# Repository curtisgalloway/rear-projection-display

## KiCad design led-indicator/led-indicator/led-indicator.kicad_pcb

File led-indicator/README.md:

# RGBW Indicator Board — LED Indicator

KiCad 8 schematic for a 12-LED addressable RGBW indicator panel. Replaces incandescent bulbs in a rear-projection indicator display. Target: ~2×3 inch, 2-layer, JLCPCB fabrication + assembly.

## Bill of Materials

| Ref | Qty | Value / Description | Package | JLCPCB Part | Notes |
|-----|-----|---------------------|---------|-------------|-------|
| D1–D12 | 12 | SK6812 RGBW addressable LED | 5050 SMD (5.0×5.0mm) | C2890364 (SK6812-EC15) | Assign footprint `LED_SMD:LED_SK6812_PLCC4_5.0x5.0mm_P3.2mm` |
| C1–C12 | 12 | 100nF ceramic capacitor | 0603 SMD | C14663 | Per-LED decoupling, place close to each LED |
| C13 | 1 | 1000µF 10V electrolytic | Radial 8mm dia, 3.5mm pitch | C6185 (100µF) or C6971 (1000µF SMD) | Bulk input decoupling; check JLCPCB Basic parts at order time |
| R1 | 1 | 330Ω resistor | 0603 SMD | C23138 | Data line series resistor (DIN protection) |
| U1 | 1 | 74AHCT125 quad 3-state buffer | SOIC-14 | C7084 | 3.3V→5V level shifter; Basic part |
| J1 | 1 | DC barrel jack 2.1mm×5.5mm, center-positive | Through-hole | — | PJ-102AH or equivalent; assign footprint manually |
| J2 | 1 | JST-XH 3-pin header (5V, GND, DATA) | Through-hole, 2.5mm pitch | C2681542 | Pin 1=5V (via SJ1), Pin 2=GND, Pin 3=DATA |
| SJ1 | 1 | Solder jumper, 2-pin, normally OPEN | — | — | Isolates J2 5V pin from main rail; close to back-power from controller |

## Schematic Notes

**Daisy-chain direction:** DATA_IN → R1 → D1.DIN → D1.DOUT → D2.DIN → … → D12.DOUT (leave D12.DOUT unconnected or add test point)

**330Ω resistor (R1):** Limits current transients and protects against transmission-line reflections on the data line. Place between U1 output and D1.DIN.

**Solder jumper SJ1:** Normally open. Connects the 5V pin on J2 to the main +5V rail. Close only when powering the board from the controller side (low-power testing). Leave open when using the barrel jack (J1) to avoid fighting two supplies.

**74AHCT125 (U1):**
- Channel 1 (pins 1/2/3): active — ~OE tied to GND (pin 1), A=DATA_IN (pin 2), Y=data out to R1 (pin 3)
- Channels 2–4: disabled — ~OE pins (4, 10, 13) tied to +5V; A inputs (5, 9, 12) tied to GND; Y outputs (6, 8, 11) no-connect

## Footprints to Assign Before PCB Layout

| Ref | Footprint |
|-----|-----------|
| D1–D12 | `LED_SMD:LED_SK6812_PLCC4_5.0x5.0mm_P3.2mm` *(already set)* |
| J1 | `Connector_BarrelJack:BarrelJack_Horizontal_PJ-102AH` or similar 2.1mm barrel |
| SJ1 | `Jumper:SolderJumper-2_P1.3mm_Open_Pad1.0x1.5mm` |
| C13 | Verify package matches the part ordered (radial THT or SMD) |

## Power Budget (rough)

SK6812 at full white: ~60mA per LED × 12 = 720mA + 5V logic overhead. Use a ≥1A 5V supply on J1. The 1000µF bulk cap (C13) handles the high-frequency current draw of the WS2812-protocol burst updates.

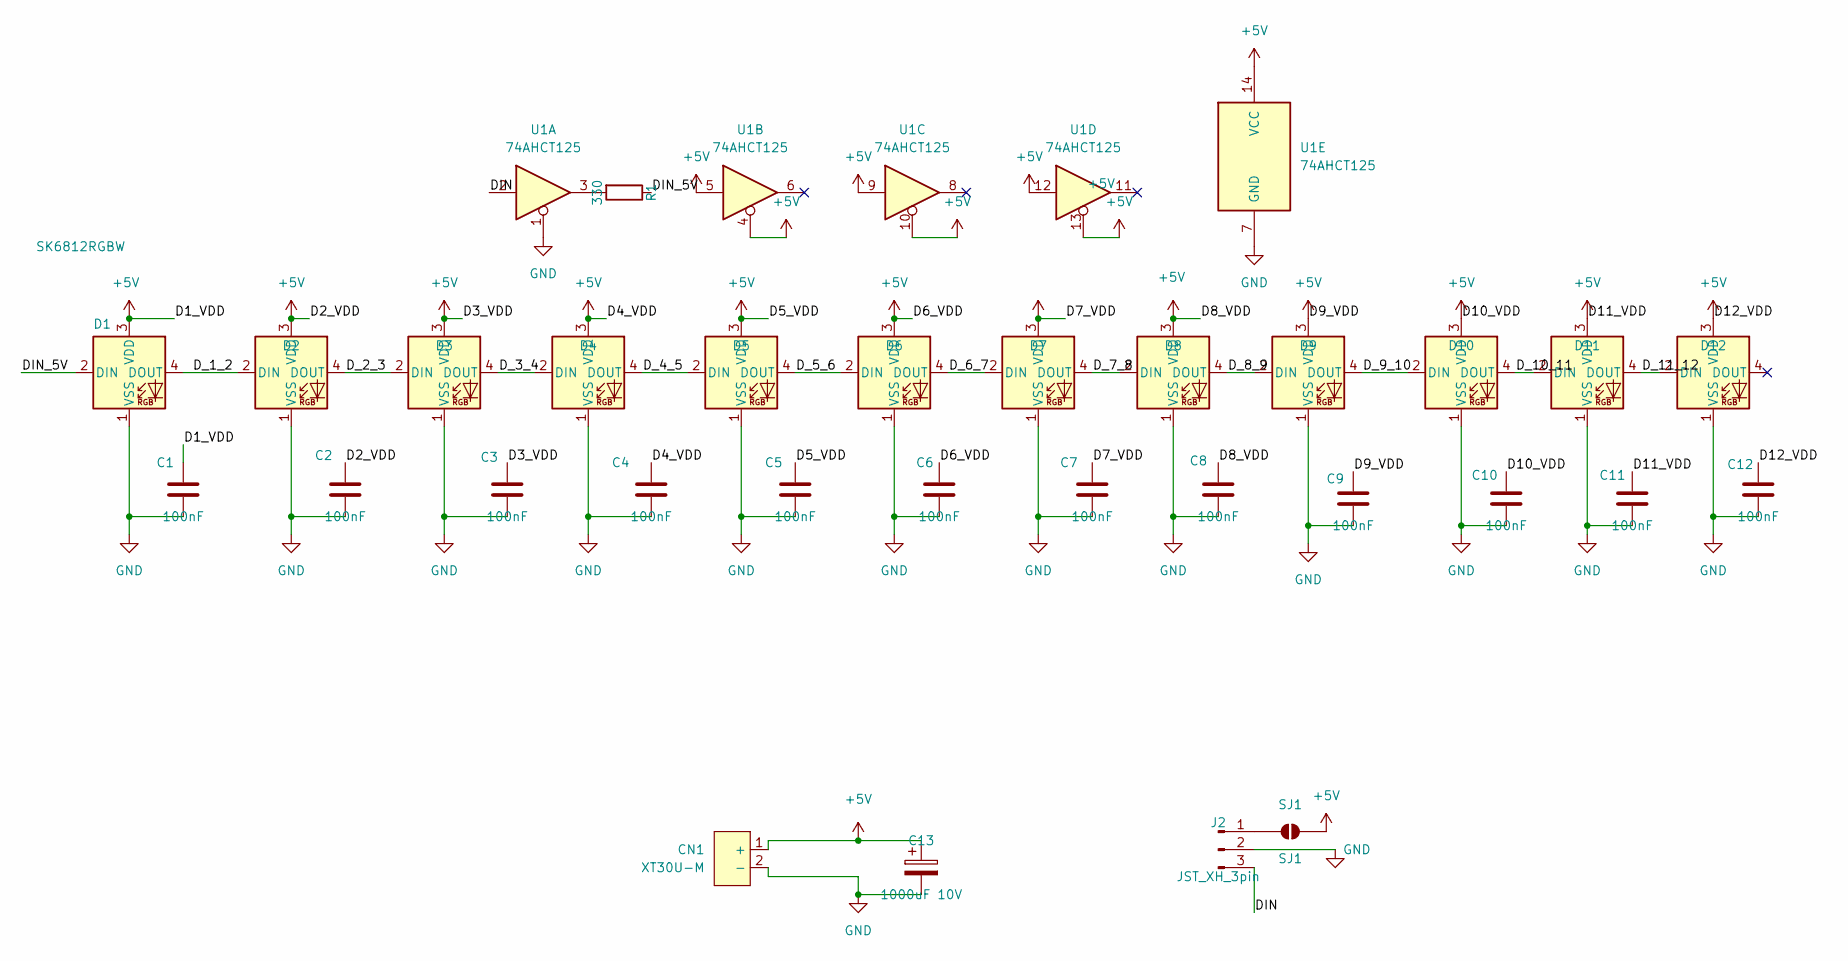
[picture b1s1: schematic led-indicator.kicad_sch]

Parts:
C1, C2, C3, C4, C5, C6, C7, C8, C9, C10, C11, C12: 100nF; C_0603_1608Metric; MPN CC0603KRX7R9BB104; LCSC C14663
C13: 1000uF 10V; CP_Radial_D8.0mm_P3.50mm; MPN GR108M010F12RR0VL4FP0; LCSC C3299
CN1: XT30U-M; AMASS_XT30U-M_1x02_P5.0mm_Vertical; MPN XT30U-M; LCSC Part C99101
D1, D2, D3, D4, D5, D6, D7, D8, D9, D10, D11, D12: SK6812RGBW; LED_SK6812_PLCC4_5.0x5.0mm_P3.2mm; MPN XL-5050RGBWC-WS2812B; LCSC C22464516
J2: JST_XH_3pin; JST_XH_B3B-XH-A_1x03_P2.50mm_Vertical; MPN B3B-XH-A(LF)(SN); LCSC C144394
R1: 330; R_0603_1608Metric; MPN 0603WAF3300T5E; LCSC C23138
SJ1: SJ1; SolderJumper-2_P1.3mm_Open_RoundedPad1.0x1.5mm
U1: 74AHCT125; SOIC-14_3.9x8.7mm_P1.27mm; MPN 74AHCT125S14-13; LCSC C842299

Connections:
+5V: C1.1, C2.1, C3.1, C4.1, C5.1, C6.1, C7.1, C8.1, C9.1, C10.1, C11.1, C12.1, C13.1, CN1.1 (+), D1.3 (VDD), D2.3 (VDD), D3.3 (VDD), D4.3 (VDD), D5.3 (VDD), D6.3 (VDD), D7.3 (VDD), D8.3 (VDD), D9.3 (VDD), D10.3 (VDD), D11.3 (VDD), D12.3 (VDD), SJ1.2 (B), U1.4, U1.5, U1.9, U1.10, U1.12, U1.13, U1.14 (VCC)
/DIN: J2.3, U1.2
/DIN_5V: D1.2 (DIN), R1.1
/D_1_2: D1.4 (DOUT), D2.2 (DIN)
/D_2_3: D2.4 (DOUT), D3.2 (DIN)
/D_3_4: D3.4 (DOUT), D4.2 (DIN)
/D_4_5: D4.4 (DOUT), D5.2 (DIN)
/D_5_6: D5.4 (DOUT), D6.2 (DIN)
/D_6_7: D6.4 (DOUT), D7.2 (DIN)
/D_7_8: D7.4 (DOUT), D8.2 (DIN)
/D_8_9: D8.4 (DOUT), D9.2 (DIN)
/D_9_10: D9.4 (DOUT), D10.2 (DIN)
/D_10_11: D10.4 (DOUT), D11.2 (DIN)
/D_11_12: D11.4 (DOUT), D12.2 (DIN)
GND: C1.2, C2.2, C3.2, C4.2, C5.2, C6.2, C7.2, C8.2, C9.2, C10.2, C11.2, C12.2, C13.2, CN1.2 (-), D1.1 (VSS), D2.1 (VSS), D3.1 (VSS), D4.1 (VSS), D5.1 (VSS), D6.1 (VSS), D7.1 (VSS), D8.1 (VSS), D9.1 (VSS), D10.1 (VSS), D11.1 (VSS), D12.1 (VSS), J2.2, U1.1, U1.7 (GND)
unnamed: J2.1, SJ1.1 (A)
unnamed: R1.2, U1.3

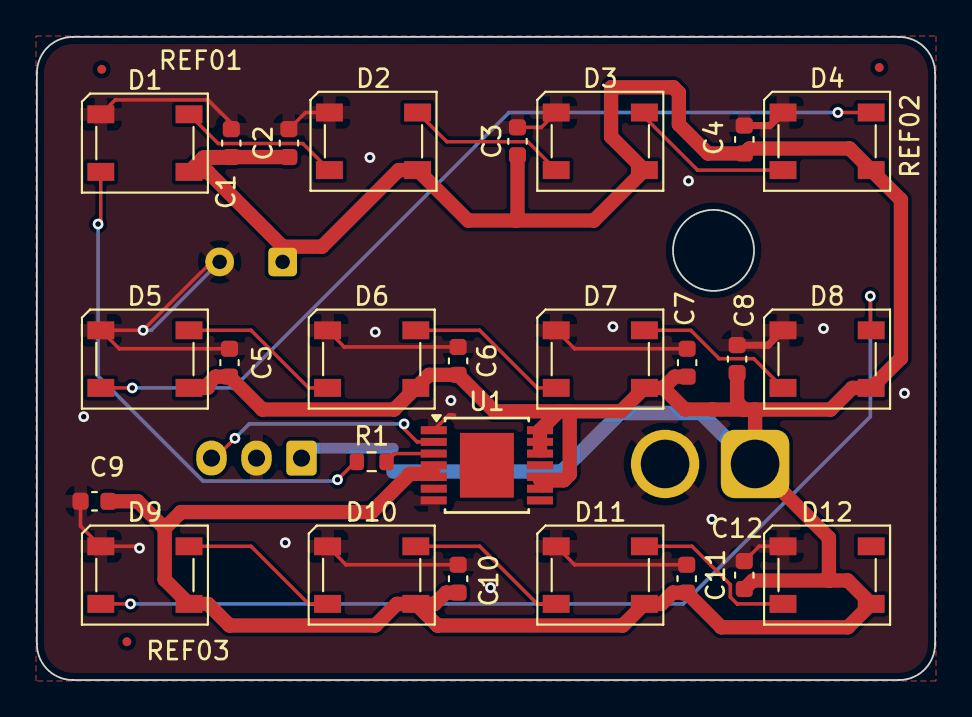
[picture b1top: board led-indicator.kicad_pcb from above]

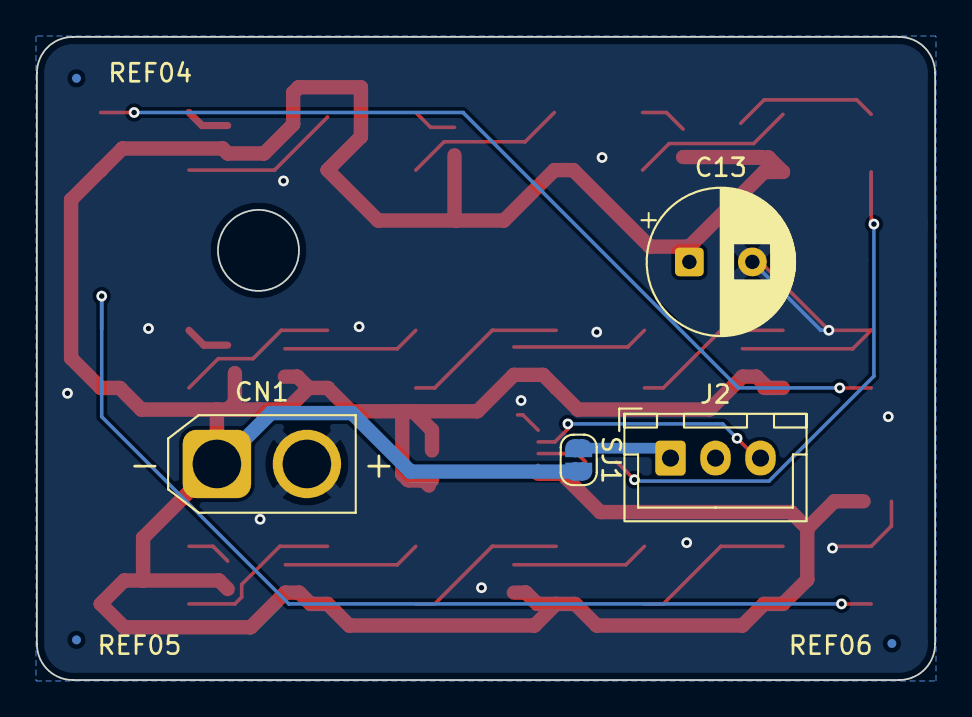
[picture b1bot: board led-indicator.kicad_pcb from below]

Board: 2 copper layers, 49.9 x 35.7 mm, 36 parts (7 on the bottom side), 17 nets.

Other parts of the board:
REF01, REF02, REF03, REF04, REF05, REF06: Fiducial_0.5mm_Mask1mm

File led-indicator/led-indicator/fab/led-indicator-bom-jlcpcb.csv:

Comment,Designator,Footprint,LCSC Part #
100nF,"C1,C2,C3,C4,C5,C6,C7,C8,C9,C10,C11,C12",Capacitor_SMD:C_0603_1608Metric,C14663
SK6812RGBW,"D1,D2,D3,D4,D5,D6,D7,D8,D9,D10,D11,D12",LED_SMD:LED_SK6812_PLCC4_5.0x5.0mm_P3.2mm,C22464516
JST_XH_3pin,J2,Connector_JST:JST_XH_B3B-XH-A_1x03_P2.50mm_Vertical,C144394
330,R1,Resistor_SMD:R_0603_1608Metric,C23138
74AHCT125,U1,Package_SO:SOIC-14_3.9x8.7mm_P1.27mm,C842299
1000uF 10V,C13,Capacitor_THT:CP_Radial_D8.0mm_P3.50mm,C3299
XT30U-M,CN1,Connector_AMASS:AMASS_XT30U-M_1x02_P5.0mm_Vertical,C99101

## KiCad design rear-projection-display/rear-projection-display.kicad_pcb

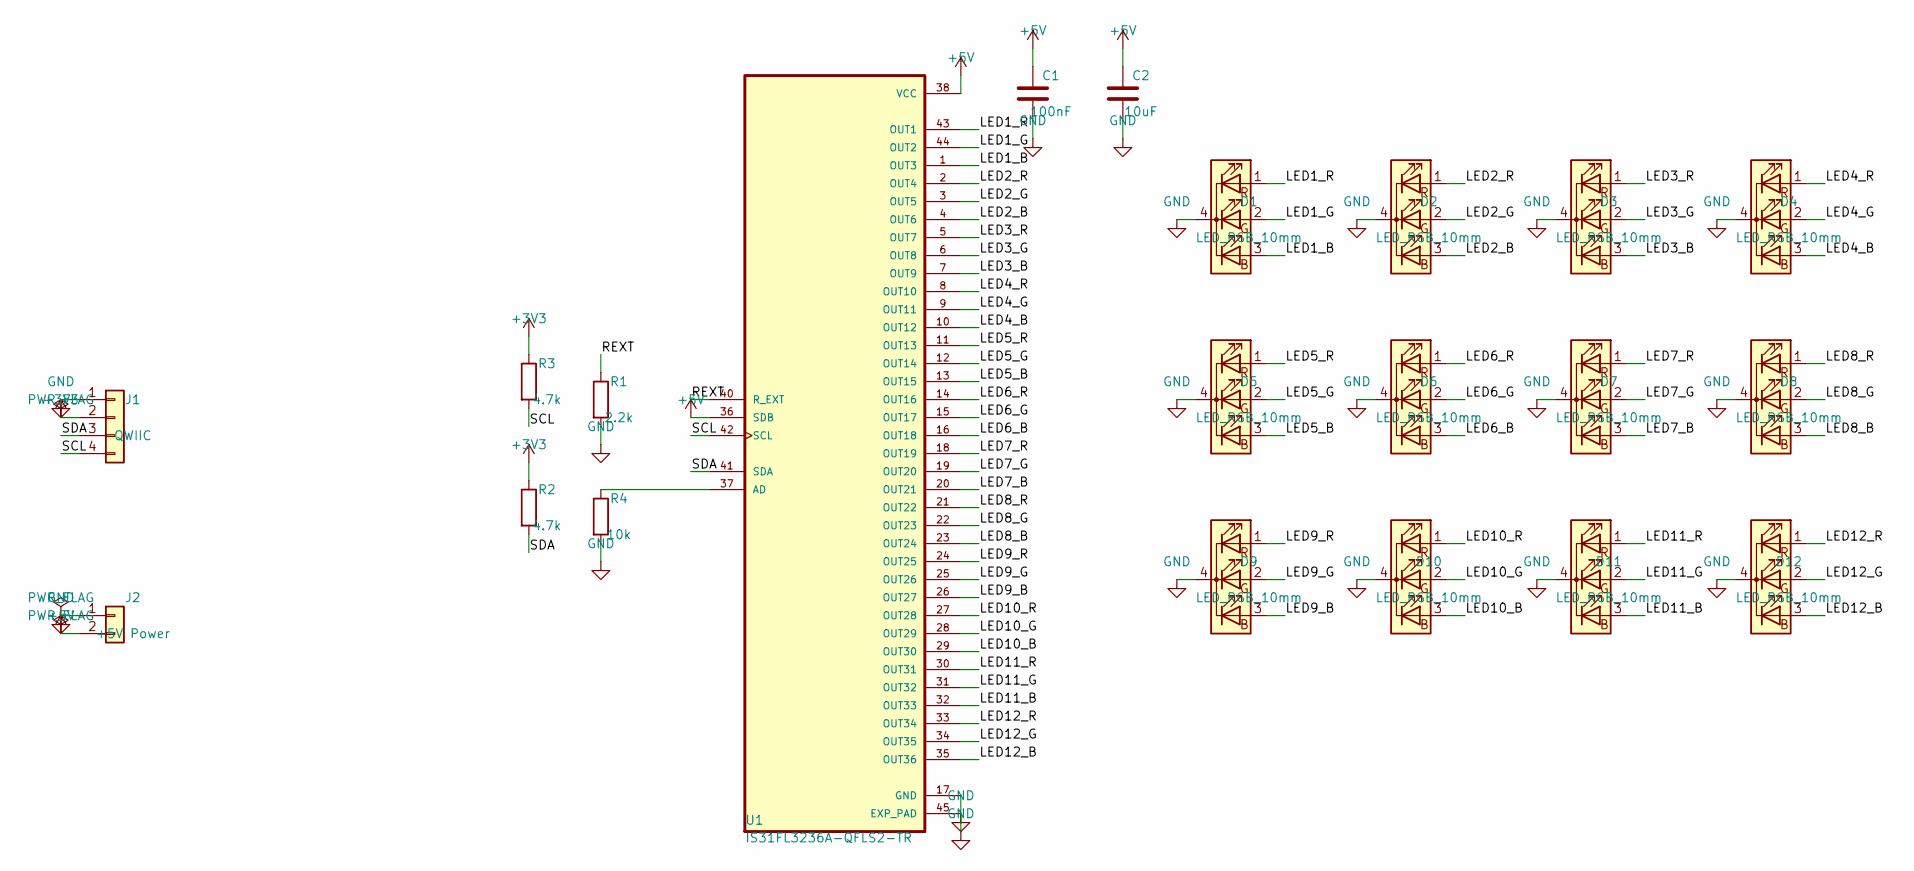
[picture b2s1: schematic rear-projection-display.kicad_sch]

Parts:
C1: 100nF; C_0402_1005Metric
C2: 10uF; C_0805_2012Metric
D1, D2, D3, D4, D5, D6, D7, D8, D9, D10, D11, D12: LED_RGB_10mm; LED_RGB_10mm_4pin
J1: QWIIC; JST_SH_BM04B-SRSS-TB_1x04-1MP_P1.00mm_Vertical
J2: +5V Power; PinHeader_1x02_P2.54mm_Vertical
R1: 2.2k; R_0603_1608Metric
R2, R3: 4.7k; R_0603_1608Metric
R4: 10k; R_0603_1608Metric
U1: IS31FL3236A-QFLS2-TR; QFN40P500X500X80-45N; LCSC C246443

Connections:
/LED1_B: D1.3 (BA), U1.1 (OUT3)
/LED1_G: D1.2 (GA), U1.44 (OUT2)
/LED1_R: D1.1 (RA), U1.43 (OUT1)
/LED2_B: D2.3 (BA), U1.4 (OUT6)
/LED2_G: D2.2 (GA), U1.3 (OUT5)
/LED2_R: D2.1 (RA), U1.2 (OUT4)
/LED3_B: D3.3 (BA), U1.7 (OUT9)
/LED3_G: D3.2 (GA), U1.6 (OUT8)
/LED3_R: D3.1 (RA), U1.5 (OUT7)
/LED4_B: D4.3 (BA), U1.10 (OUT12)
/LED4_G: D4.2 (GA), U1.9 (OUT11)
/LED4_R: D4.1 (RA), U1.8 (OUT10)
/LED5_B: D5.3 (BA), U1.13 (OUT15)
/LED5_G: D5.2 (GA), U1.12 (OUT14)
/LED5_R: D5.1 (RA), U1.11 (OUT13)
/LED6_B: D6.3 (BA), U1.16 (OUT18)
/LED6_G: D6.2 (GA), U1.15 (OUT17)
/LED6_R: D6.1 (RA), U1.14 (OUT16)
/LED7_B: D7.3 (BA), U1.20 (OUT21)
/LED7_G: D7.2 (GA), U1.19 (OUT20)
/LED7_R: D7.1 (RA), U1.18 (OUT19)
/LED8_B: D8.3 (BA), U1.23 (OUT24)
/LED8_G: D8.2 (GA), U1.22 (OUT23)
/LED8_R: D8.1 (RA), U1.21 (OUT22)
/LED9_B: D9.3 (BA), U1.26 (OUT27)
/LED9_G: D9.2 (GA), U1.25 (OUT26)
/LED9_R: D9.1 (RA), U1.24 (OUT25)
/LED10_B: D10.3 (BA), U1.29 (OUT30)
/LED10_G: D10.2 (GA), U1.28 (OUT29)
/LED10_R: D10.1 (RA), U1.27 (OUT28)
/LED11_B: D11.3 (BA), U1.32 (OUT33)
/LED11_G: D11.2 (GA), U1.31 (OUT32)
/LED11_R: D11.1 (RA), U1.30 (OUT31)
/LED12_B: D12.3 (BA), U1.35 (OUT36)
/LED12_G: D12.2 (GA), U1.34 (OUT35)
/LED12_R: D12.1 (RA), U1.33 (OUT34)
/REXT: R1.1, U1.40 (R_EXT)
/SCL: J1.4, R3.2, U1.42 (SCL)
/SDA: J1.3, R2.2, U1.41 (SDA)
unnamed: R4.1, U1.37 (AD)

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
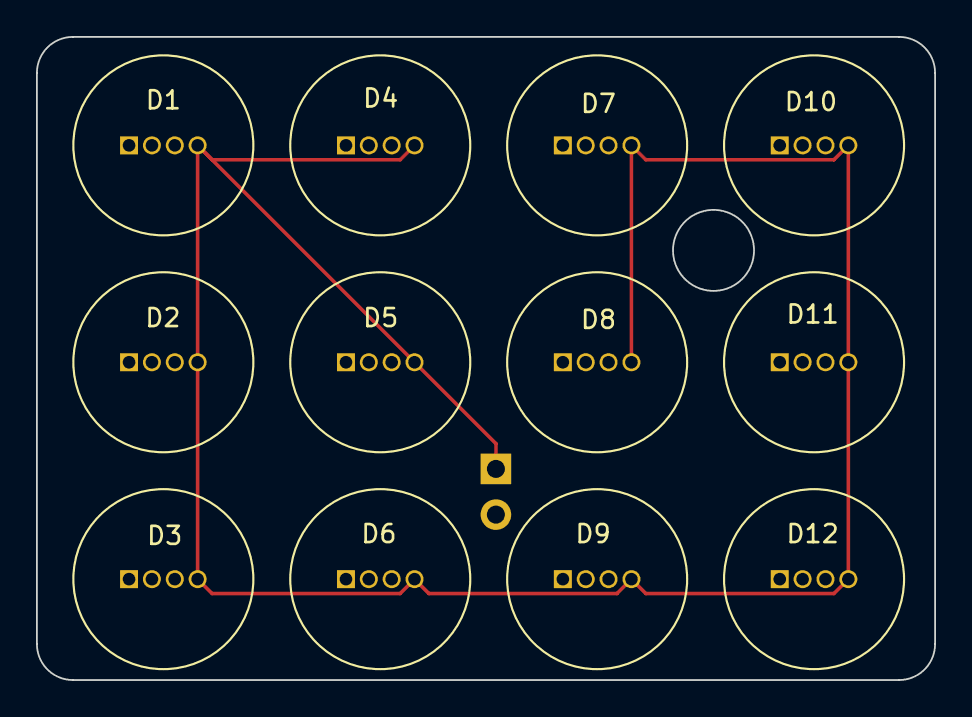
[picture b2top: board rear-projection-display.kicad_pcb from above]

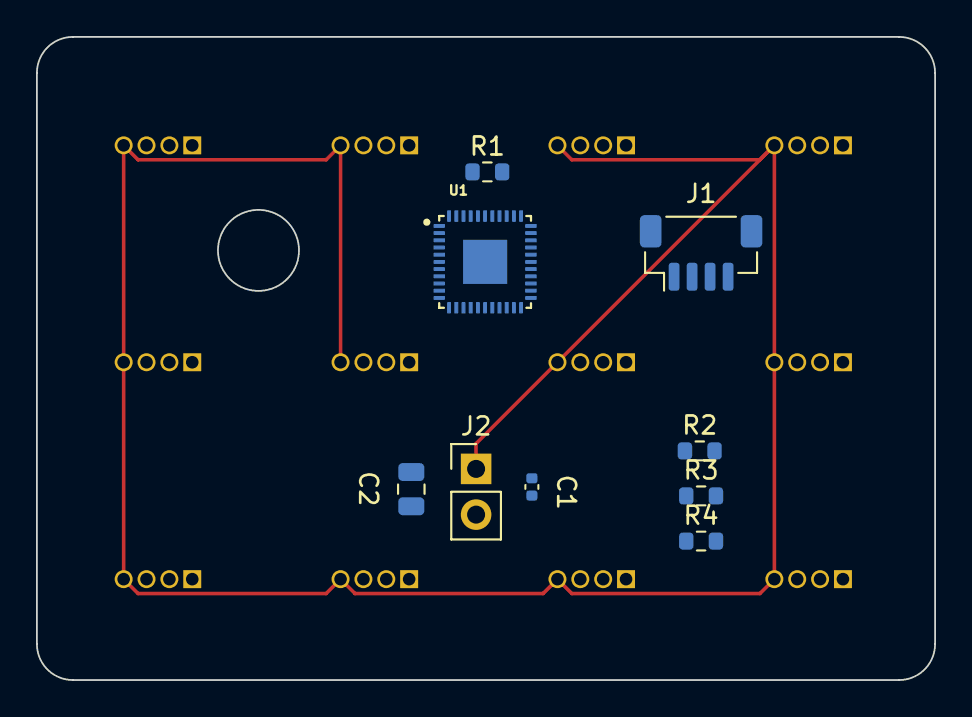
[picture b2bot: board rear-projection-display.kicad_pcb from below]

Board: 2 copper layers, 49.9 x 35.7 mm, 21 parts (9 on the bottom side), 43 nets.

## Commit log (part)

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2026-05-11 Remove first try at making a board with through-hole LEDs.
2026-05-16 Updated to be single-sided board.
